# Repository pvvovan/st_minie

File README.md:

# minie adapter
STLINK-V3MINIE JTAG/SWD/UART adapter

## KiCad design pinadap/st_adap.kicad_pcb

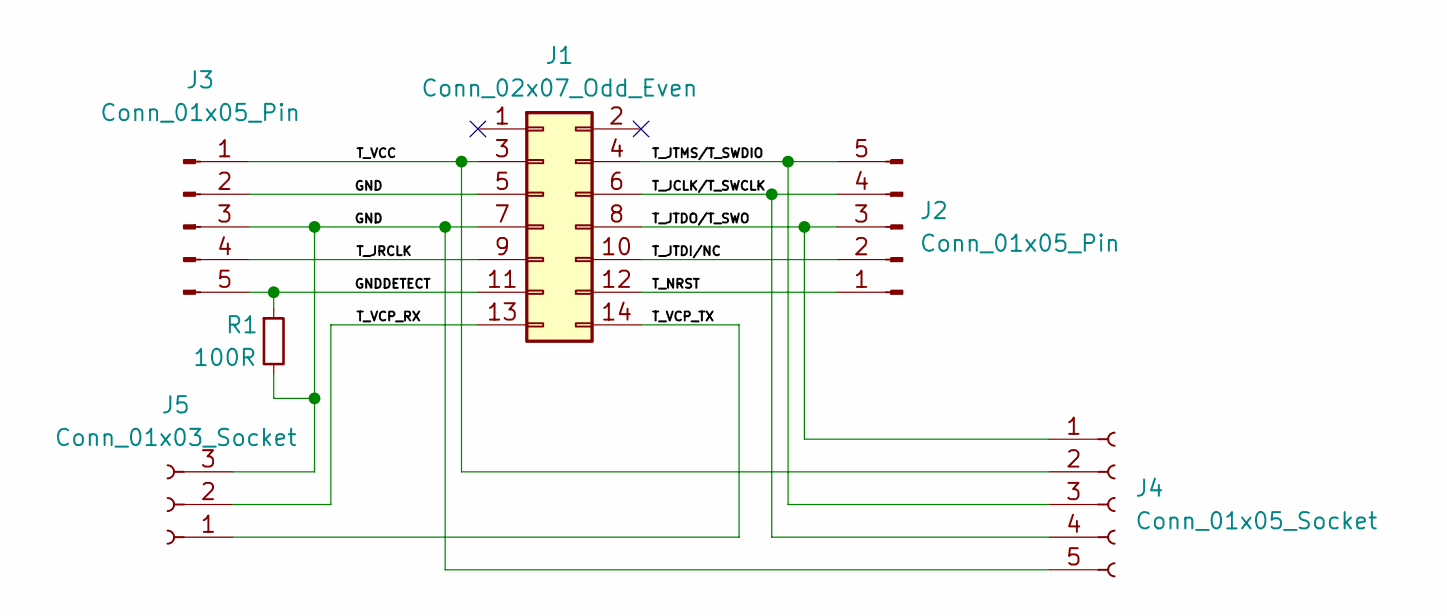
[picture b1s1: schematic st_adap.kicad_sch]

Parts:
J1: Conn_02x07_Odd_Even; PinHeader_2x07_P1.27mm_Vertical_SMD
J2, J3: Conn_01x05_Pin; PinHeader_1x05_P2.54mm_Vertical
J4: Conn_01x05_Socket; PinSocket_1x05_P2.54mm_Vertical
J5: Conn_01x03_Socket; PinSocket_1x03_P2.54mm_Vertical
R1: 100R; R_0805_2012Metric_Pad1.20x1.40mm_HandSolder; JLC# C17408

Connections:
/GND: J1.5, J1.7, J3.2, J3.3, J4.5, J5.3, R1.2
/GNDDETECT: J1.11, J3.5, R1.1
/T_JCLK/T_SWCLK: J1.6, J2.4, J4.4
/T_JRCLK: J1.9, J3.4
/T_JTDI/NC: J1.10, J2.2
/T_JTDO/T_SWO: J1.8, J2.3, J4.1
/T_JTMS/T_SWDIO: J1.4, J2.5, J4.3
/T_NRST: J1.12, J2.1
/T_VCC: J1.3, J3.1, J4.2
/T_VCP_RX: J1.13, J5.2
/T_VCP_TX: J1.14, J5.1

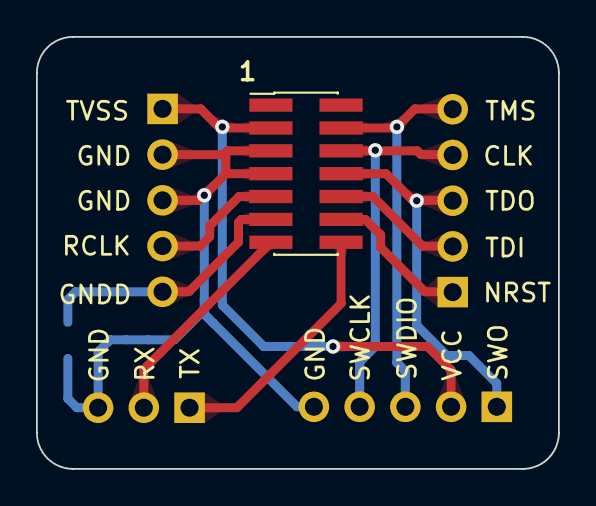
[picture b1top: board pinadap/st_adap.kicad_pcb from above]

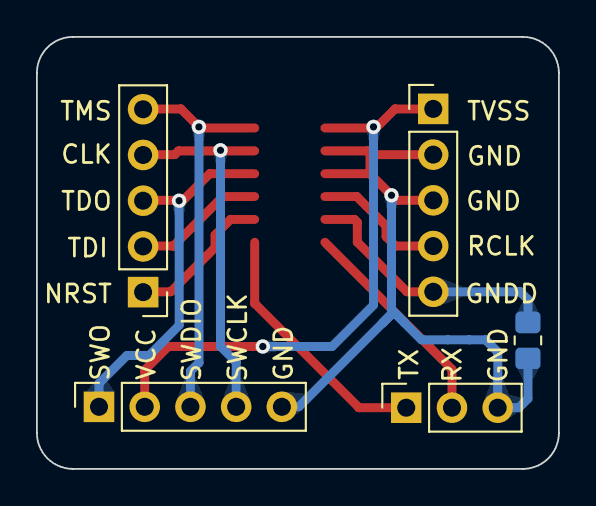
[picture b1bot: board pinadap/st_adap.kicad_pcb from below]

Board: 2 copper layers, 29.0 x 24.0 mm, 6 parts (5 on the bottom side), 11 nets.

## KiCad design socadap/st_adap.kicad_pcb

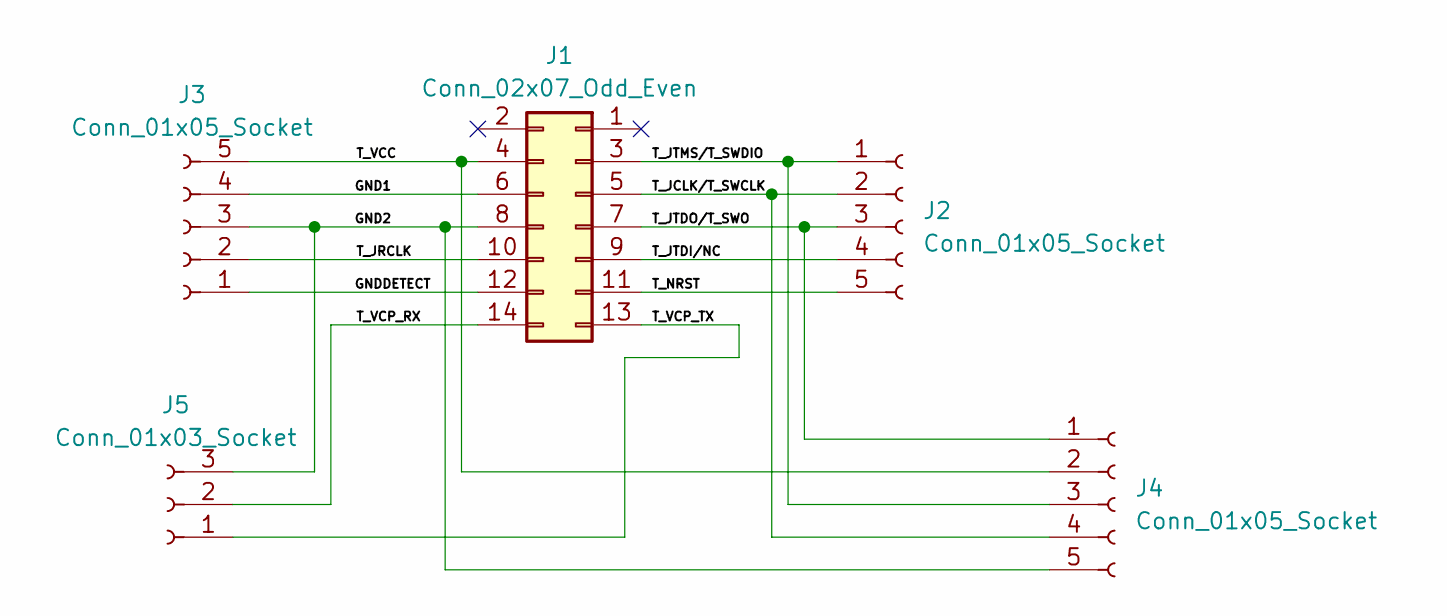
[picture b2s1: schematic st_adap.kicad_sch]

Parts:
J1: Conn_02x07_Odd_Even; PinSocket_2x07_P1.27mm_Vertical; JLC# C2881912
J2, J3: Conn_01x05_Socket; PinHeader_1x05_P2.54mm_Vertical
J4: Conn_01x05_Socket; PinSocket_1x05_P2.54mm_Vertical
J5: Conn_01x03_Socket; PinSocket_1x03_P2.54mm_Vertical

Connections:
/GND1: J1.6, J3.4
/GND2: J1.8, J3.3, J4.5, J5.3
/GNDDETECT: J1.12, J3.1
/T_JCLK/T_SWCLK: J1.5, J2.2, J4.4
/T_JRCLK: J1.10, J3.2
/T_JTDI/NC: J1.9, J2.4
/T_JTDO/T_SWO: J1.7, J2.3, J4.1
/T_JTMS/T_SWDIO: J1.3, J2.1, J4.3
/T_NRST: J1.11, J2.5
/T_VCC: J1.4, J3.5, J4.2
/T_VCP_RX: J1.14, J5.2
/T_VCP_TX: J1.13, J5.1

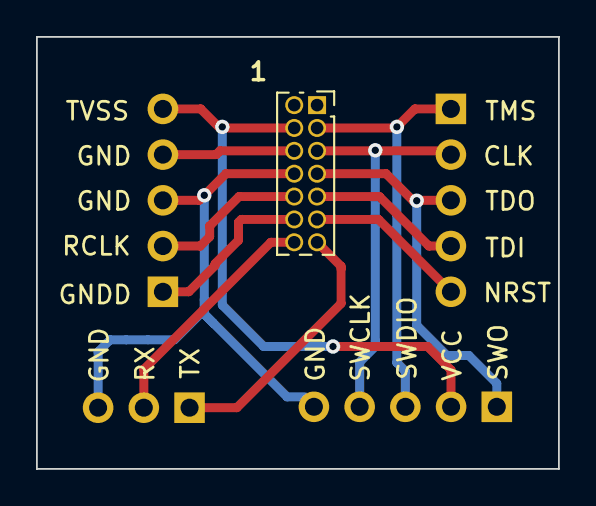
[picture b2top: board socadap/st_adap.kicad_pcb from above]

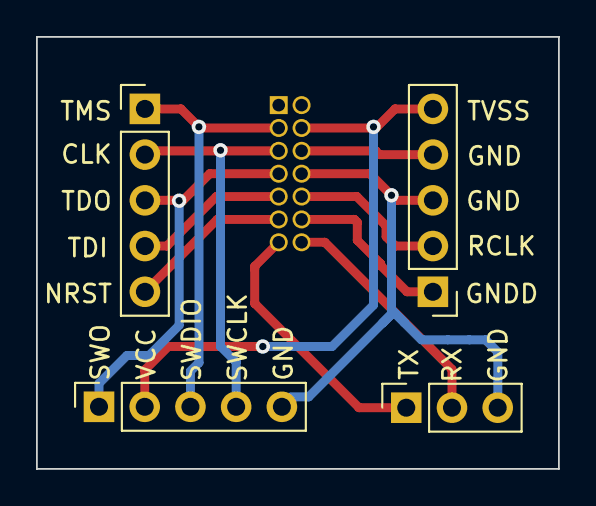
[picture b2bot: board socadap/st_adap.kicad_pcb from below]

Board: 2 copper layers, 29.0 x 24.0 mm, 5 parts (4 on the bottom side), 12 nets.

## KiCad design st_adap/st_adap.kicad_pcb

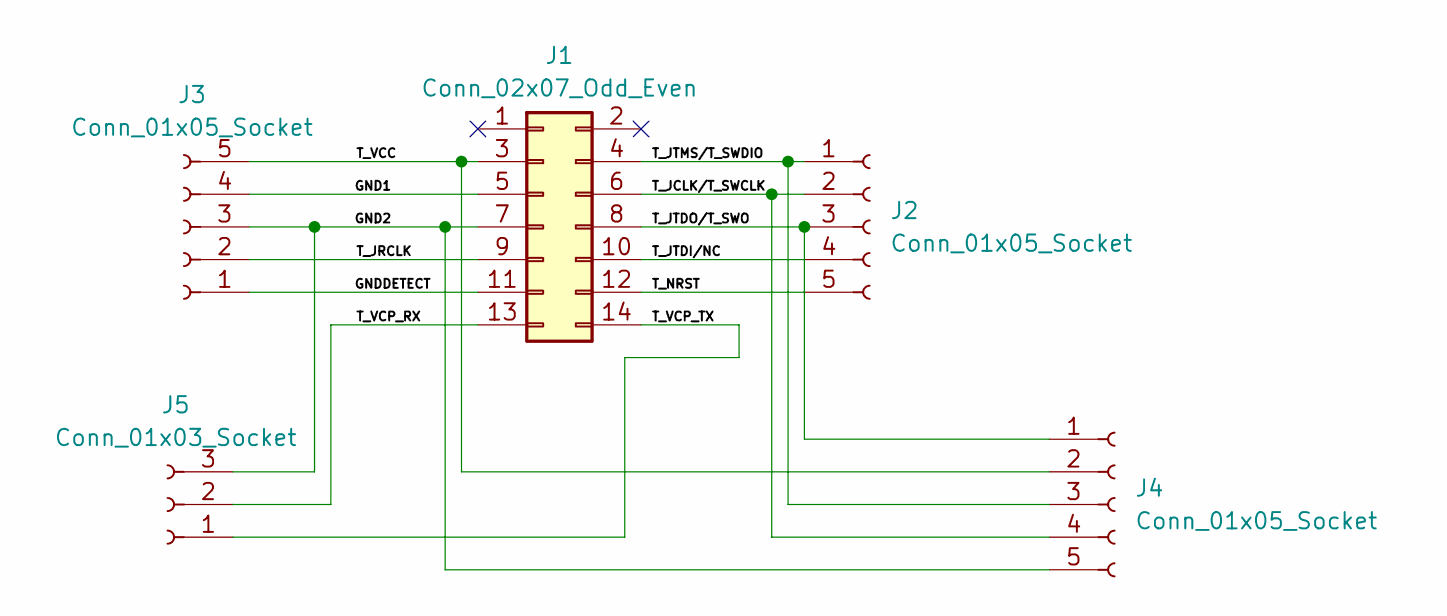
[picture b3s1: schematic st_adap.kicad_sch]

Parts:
J1: Conn_02x07_Odd_Even; PinHeader_2x07_P1.27mm_Vertical_SMD; JLC# C2881912
J2, J3: Conn_01x05_Socket; PinHeader_1x05_P2.54mm_Vertical
J4: Conn_01x05_Socket; PinSocket_1x05_P2.54mm_Vertical
J5: Conn_01x03_Socket; PinSocket_1x03_P2.54mm_Vertical

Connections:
/GND1: J1.5, J3.4
/GND2: J1.7, J3.3, J4.5, J5.3
/GNDDETECT: J1.11, J3.1
/T_JCLK/T_SWCLK: J1.6, J2.2, J4.4
/T_JRCLK: J1.9, J3.2
/T_JTDI/NC: J1.10, J2.4
/T_JTDO/T_SWO: J1.8, J2.3, J4.1
/T_JTMS/T_SWDIO: J1.4, J2.1, J4.3
/T_NRST: J1.12, J2.5
/T_VCC: J1.3, J3.5, J4.2
/T_VCP_RX: J1.13, J5.2
/T_VCP_TX: J1.14, J5.1

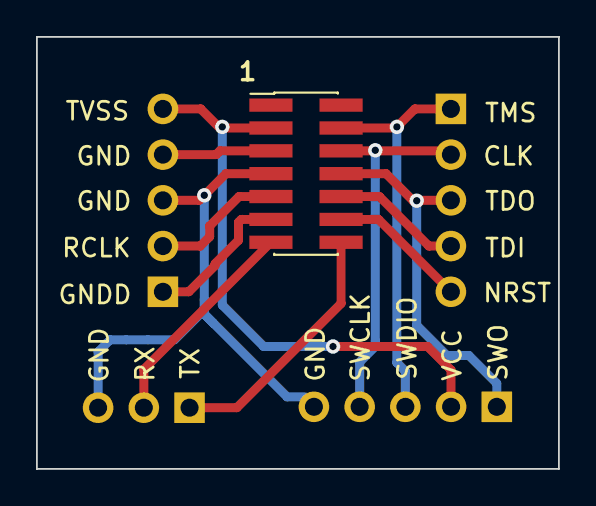
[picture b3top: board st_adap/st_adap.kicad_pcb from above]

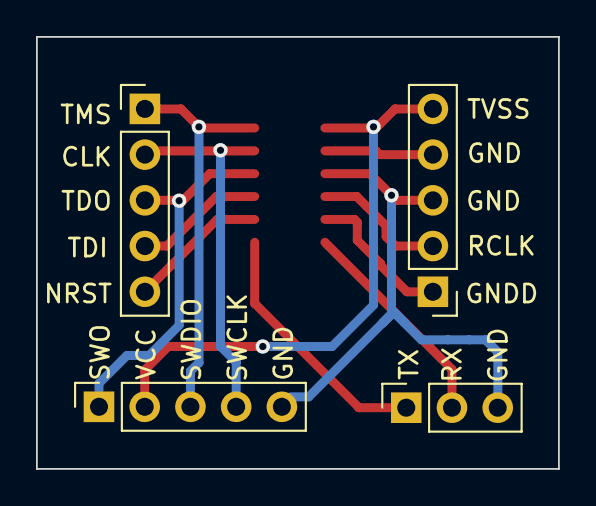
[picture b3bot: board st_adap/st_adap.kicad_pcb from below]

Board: 2 copper layers, 29.0 x 24.0 mm, 5 parts (4 on the bottom side), 12 nets.

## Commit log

2023-10-10 Initial
2023-10-10 Generate fabrication files
2023-10-12 Clean temporary/generated files
2023-10-12 Add generation script for JLCPCB
2023-10-12 Generate gerber files
2023-10-12 JLCPCB files
2023-10-12 Add 3D view screenshots
2023-10-12 Rotate connector
2023-10-13 Initial socadap
2023-10-13 Socket 2x7
2023-10-13 Gen socadp
2023-10-21 Regenerate pin adaptor
2024-02-23 1.27mm connector with key
2024-02-24 Remove unused
2024-02-24 Update 3D screenshot
